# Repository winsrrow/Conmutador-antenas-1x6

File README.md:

# Conmutador antenas 1x6
Conmutador de antenas 1x6 con raspberry pi pico 2W

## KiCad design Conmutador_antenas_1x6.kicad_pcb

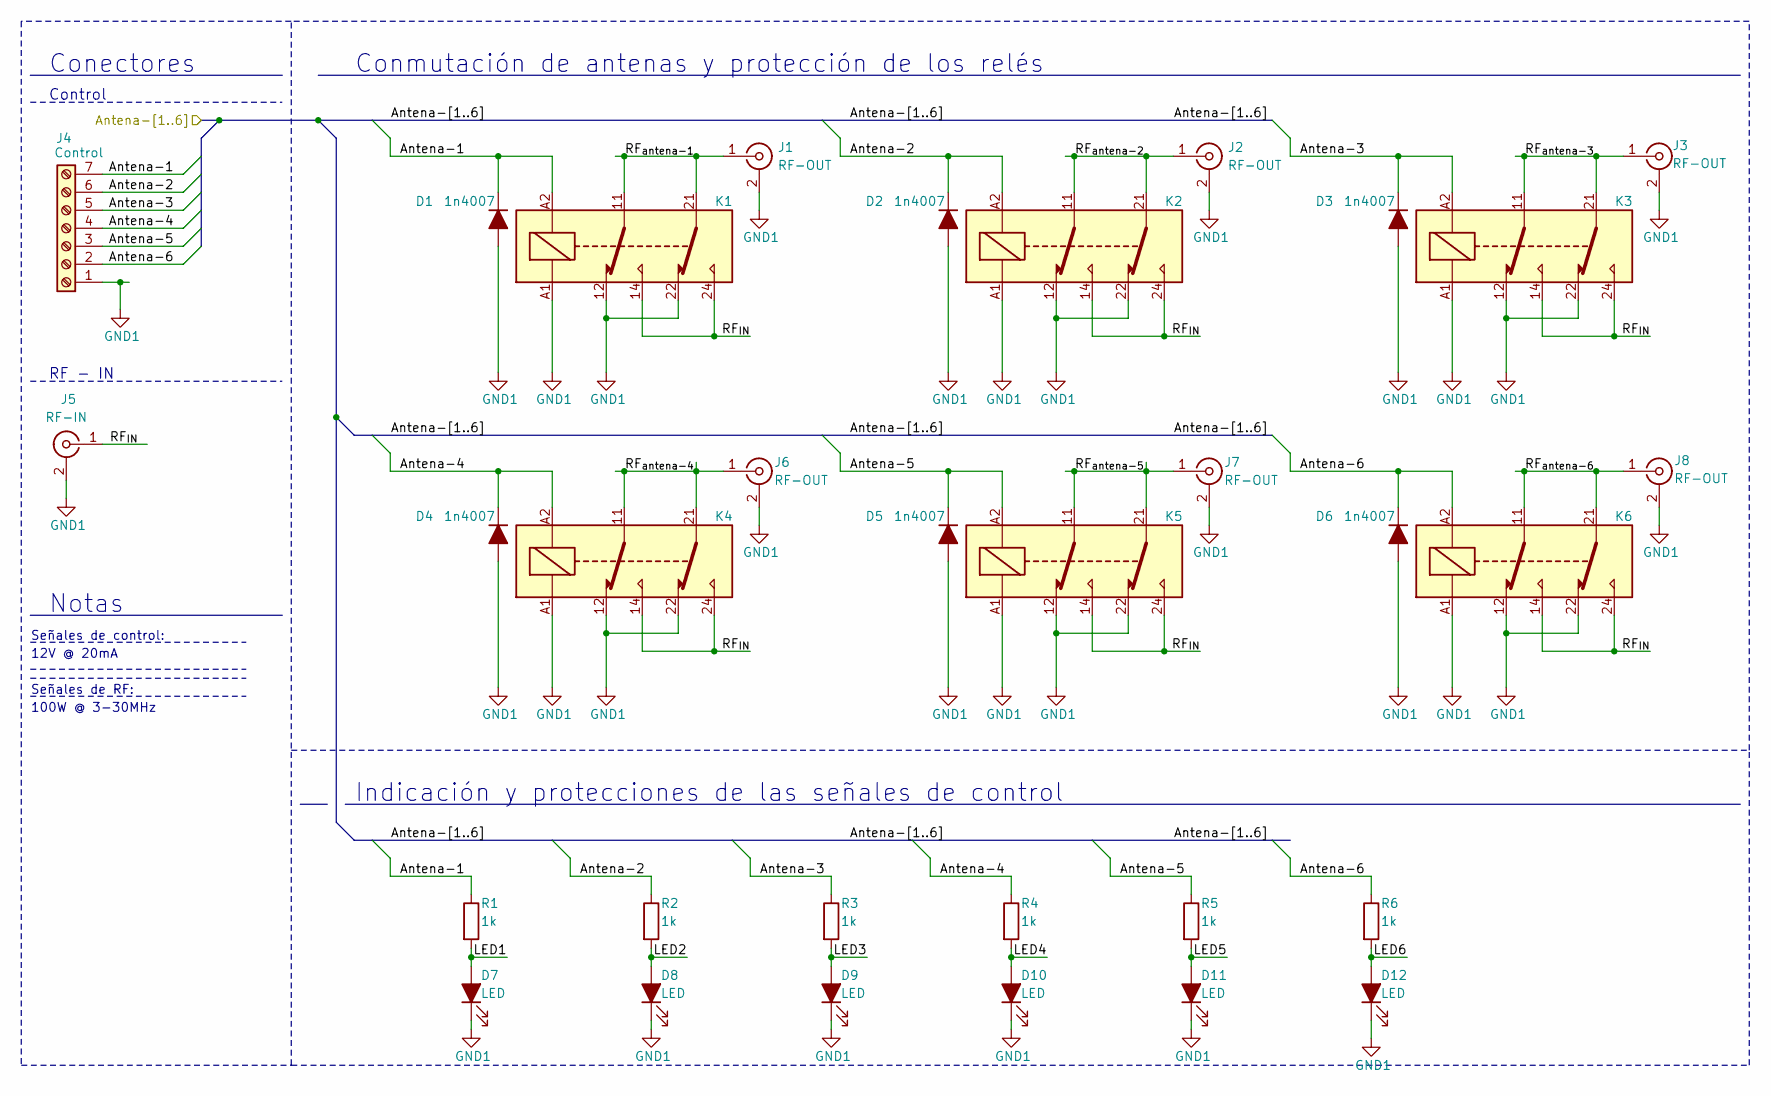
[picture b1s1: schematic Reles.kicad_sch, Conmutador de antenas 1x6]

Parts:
D1, D2, D3, D4, D5, D6: 1n4007; D_DO-41_SOD81_P7.62mm_Horizontal
D7, D8, D9, D10, D11, D12: LED; LED_D3.0mm
J1, J2, J3, J5, J6, J7, J8: Conn_Coaxial; SO-239
J4: Screw_Terminal_01x07; TerminalBlock_Phoenix_MKDS-1,5-7-5.08_1x07_P5.08mm_Horizont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
K1, K2, K3, K4, K5, K6: Relay_DPDT_Schrack-RT2-FormC_RM5mm
R1, R2, R3, R4, R5, R6: 1k; R_Axial_DIN0204_L3.6mm_D1.6mm_P5.08mm_Horizontal

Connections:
/Controlador/OUT_{1}: D1.1 (K), J4.7, K1.A2, R1.1; also elsewhere on the board
/Controlador/OUT_{2}: D2.1 (K), J4.6, K2.A2, R2.1; also elsewhere on the board
/Controlador/OUT_{3}: D3.1 (K), J4.5, K3.A2, R3.1; also elsewhere on the board
/Controlador/OUT_{4}: D4.1 (K), J4.4, K4.A2, R4.1; also elsewhere on the board
/Controlador/OUT_{5}: D5.1 (K), J4.3, K5.A2, R5.1; also elsewhere on the board
/Controlador/OUT_{6}: D6.1 (K), J4.2, K6.A2, R6.1; also elsewhere on the board
/Reles/LED1: D7.2 (A), R1.2
/Reles/LED2: D8.2 (A), R2.2
/Reles/LED3: D9.2 (A), R3.2
/Reles/LED4: D10.2 (A), R4.2
/Reles/LED5: D11.2 (A), R5.2
/Reles/LED6: D12.2 (A), R6.2
/Reles/RF_{IN}: J5.1 (In), K1.14, K1.24, K2.14, K2.24, K3.14, K3.24, K4.14, K4.24, K5.14, K5.24, K6.14, K6.24
/Reles/RF_{antena-1}: J1.1 (In), K1.11, K1.21
/Reles/RF_{antena-2}: J2.1 (In), K2.11, K2.21
/Reles/RF_{antena-3}: J3.1 (In), K3.11, K3.21
/Reles/RF_{antena-4}: J6.1 (In), K4.11, K4.21
/Reles/RF_{antena-5}: J7.1 (In), K5.11, K5.21
/Reles/RF_{antena-6}: J8.1 (In), K6.11, K6.21
GND1: D1.2 (A), D2.2 (A), D3.2 (A), D4.2 (A), D5.2 (A), D6.2 (A), D7.1 (K), D8.1 (K), D9.1 (K), D10.1 (K), D11.1 (K), D12.1 (K), J1.2 (Ext), J2.2 (Ext), J3.2 (Ext), J4.1, J5.2 (Ext), J6.2 (Ext), J7.2 (Ext), J8.2 (Ext), K1.12, K1.22, K1.A1, K2.12, K2.22, K2.A1, K3.12, K3.22, K3.A1, K4.12, K4.22, K4.A1, K5.12, K5.22, K5.A1, K6.12, K6.22, K6.A1; also elsewhere on the board

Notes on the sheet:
RF - IN
Conmutación de antenas y protección de los relés
Indicación y protecciones de las señales de control
Notas
Señales de RF:
Control
Conectores
12V @ 20mA
Señales de control:
100W @ 3-30MHz

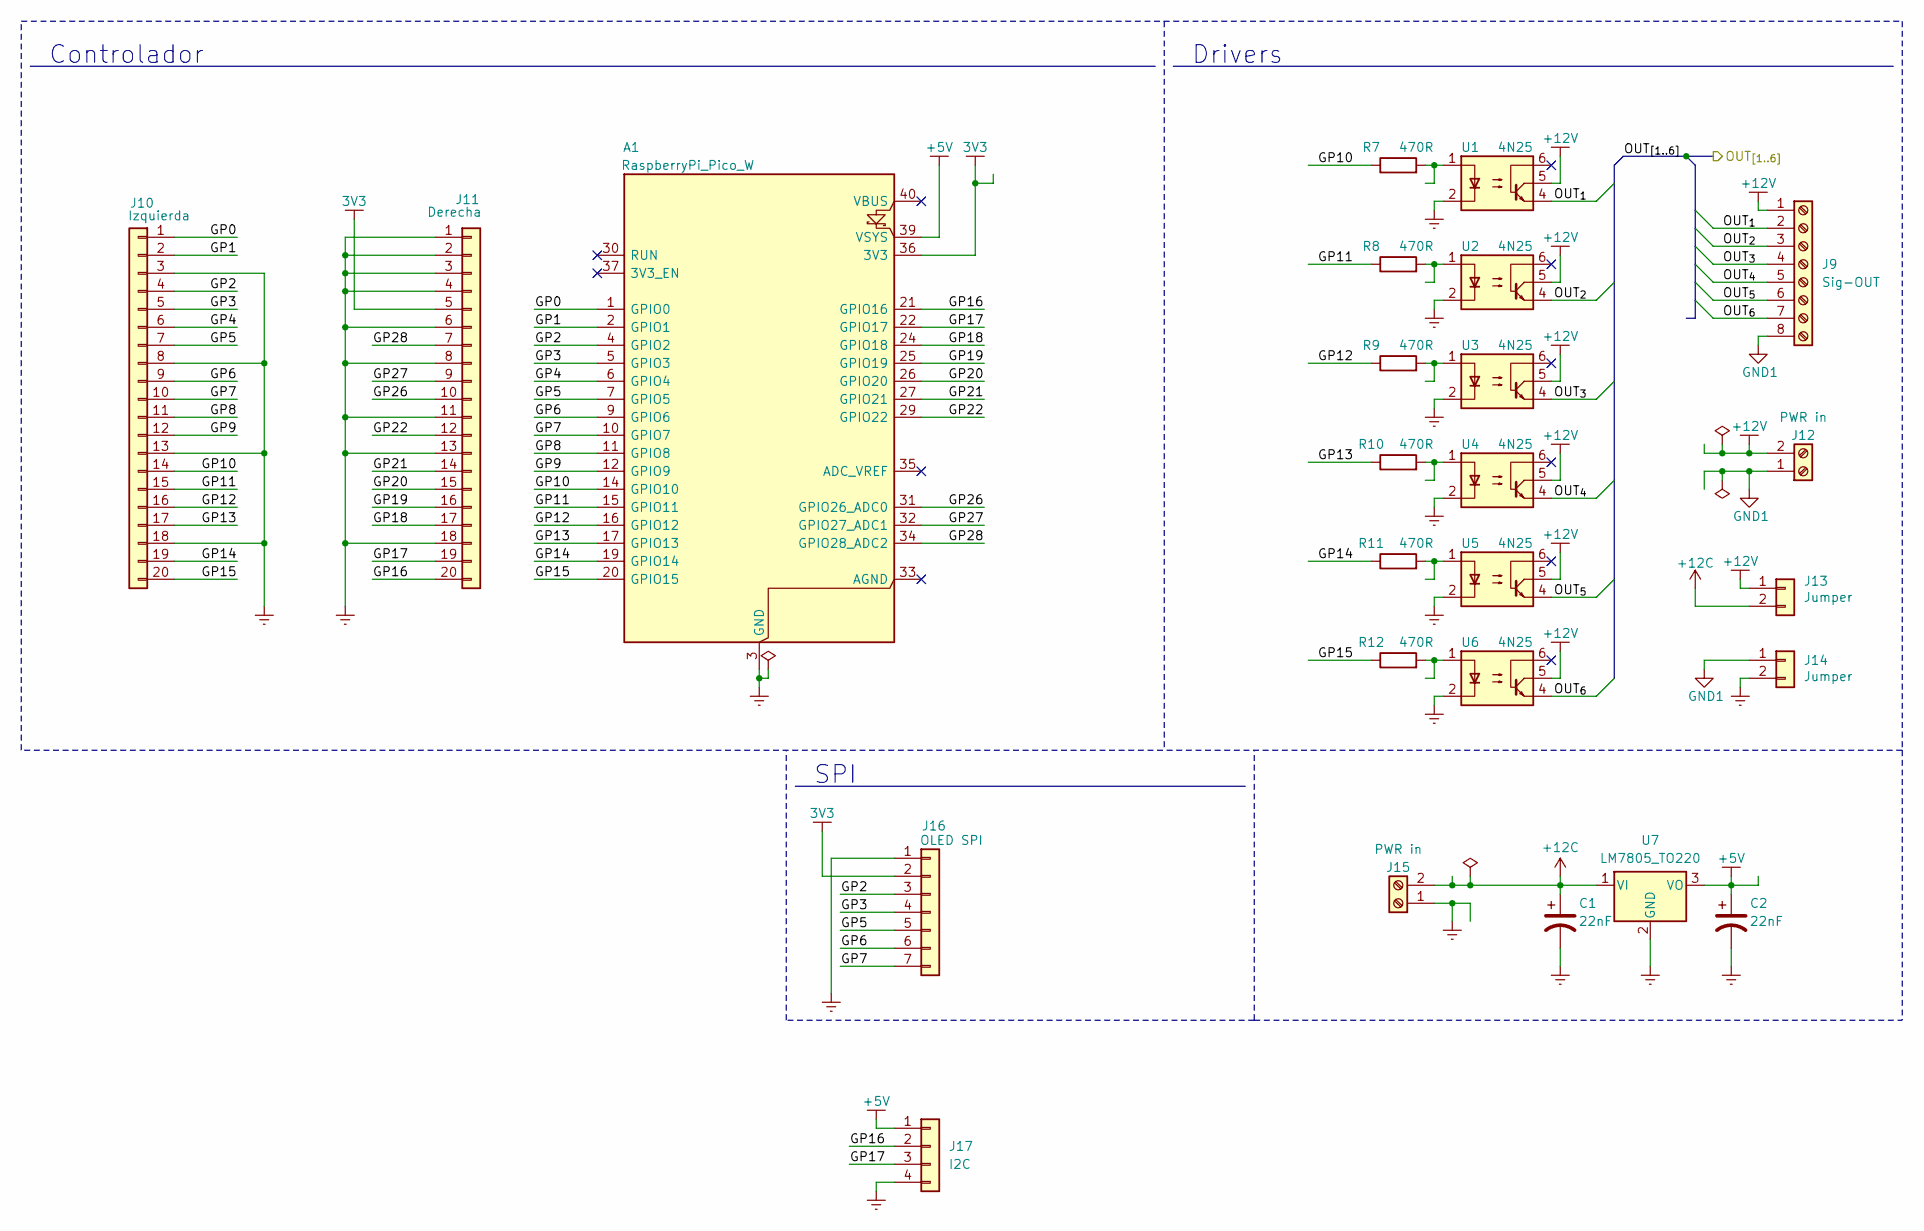
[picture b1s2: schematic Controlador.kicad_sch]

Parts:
A1: RaspberryPi_Pico_W; Pi pico 2w pin
C1, C2: 22nF; C_Disc_D5.0mm_W2.5mm_P5.00mm
J9: Screw_Terminal_01x08; TerminalBlock_Phoenix_MKDS-1,5-8-5.08_1x08_P5.08mm_Horizont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
J10, J11: Conn_01x20; PinHeader_1x20_P2.54mm_Vertical
J12, J15: Screw_Terminal_01x02; TerminalBlock_Phoenix_MKDS-1,5-2-5.08_1x02_P5.08mm_Horizont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
J13, J14: Conn_01x02; PinHeader_1x02_P2.54mm_Vertical
J16: Conn_01x07; PinHeader_1x07_P2.54mm_Vertical
J17: Conn_01x04; PinHeader_1x04_P2.54mm_Vertical
R7, R8, R9, R10, R11, R12: 470R; R_Axial_DIN0204_L3.6mm_D1.6mm_P7.62mm_Horizontal
U1, U2, U3, U4, U5, U6: 4N25; DIP-6_W7.62mm
U7: LM7805_TO220; TO-220-3_Vertical

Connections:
3V3: A1.36 (3V3), J11.5, J16.2
+5V: A1.39 (VSYS), C2.1, J17.1, U7.3 (VO)
+12C: C1.1, J13.2, J15.2, U7.1 (VI)
+12V: J9.1, J12.2, J13.1, U1.5, U2.5, U3.5, U4.5, U5.5, U6.5
/Controlador/GP0: A1.1 (GPIO0), J10.1
/Controlador/GP1: A1.2 (GPIO1), J10.2
/Controlador/GP2: A1.4 (GPIO2), J10.4, J16.3
/Controlador/GP3: A1.5 (GPIO3), J10.5, J16.4
/Controlador/GP4: A1.6 (GPIO4), J10.6
/Controlador/GP5: A1.7 (GPIO5), J10.7, J16.5
/Controlador/GP6: A1.9 (GPIO6), J10.9, J16.6
/Controlador/GP7: A1.10 (GPIO7), J10.10, J16.7
/Controlador/GP8: A1.11 (GPIO8), J10.11
/Controlador/GP9: A1.12 (GPIO9), J10.12
/Controlador/GP10: A1.14 (GPIO10), J10.14, R7.1
/Controlador/GP11: A1.15 (GPIO11), J10.15, R8.1
/Controlador/GP12: A1.16 (GPIO12), J10.16, R9.1
/Controlador/GP13: A1.17 (GPIO13), J10.17, R10.1
/Controlador/GP14: A1.19 (GPIO14), J10.19, R11.1
/Controlador/GP15: A1.20 (GPIO15), J10.20, R12.1
/Controlador/GP16: A1.21 (GPIO16), J11.20, J17.2
/Controlador/GP17: A1.22 (GPIO17), J11.19, J17.3
/Controlador/GP18: A1.24 (GPIO18), J11.17
/Controlador/GP19: A1.25 (GPIO19), J11.16
/Controlador/GP20: A1.26 (GPIO20), J11.15
/Controlador/GP21: A1.27 (GPIO21), J11.14
/Controlador/GP22: A1.29 (GPIO22), J11.12
/Controlador/GP26: A1.31 (GPIO26_ADC0), J11.10
/Controlador/GP27: A1.32 (GPIO27_ADC1), J11.9
/Controlador/GP28: A1.34 (GPIO28_ADC2), J11.7
/Controlador/OUT_{1}: J9.2, U1.4; also elsewhere on the board
/Controlador/OUT_{2}: J9.3, U2.4; also elsewhere on the board
/Controlador/OUT_{3}: J9.4, U3.4; also elsewhere on the board
/Controlador/OUT_{4}: J9.5, U4.4; also elsewhere on the board
/Controlador/OUT_{5}: J9.6, U5.4; also elsewhere on the board
/Controlador/OUT_{6}: J9.7, U6.4; also elsewhere on the board
GND: A1.3 (GND), A1.8 (GND), A1.13 (GND), A1.18 (GND), A1.23 (GND), A1.28 (GND), A1.38 (GND), C1.2, C2.2, J10.3, J10.8, J10.13, J10.18, J11.1, J11.2, J11.3, J11.4, J11.6, J11.8, J11.11, J11.13, J11.18, J14.2, J15.1, J16.1, J17.4, U1.2, U2.2, U3.2, U4.2, U5.2, U6.2, U7.2 (GND)
GND1: J9.8, J12.1, J14.1; also elsewhere on the board
unnamed: R7.2, U1.1
unnamed: R8.2, U2.1
unnamed: R9.2, U3.1
unnamed: R10.2, U4.1
unnamed: R11.2, U5.1
unnamed: R12.2, U6.1

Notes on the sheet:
Controlador
SPI
Drivers

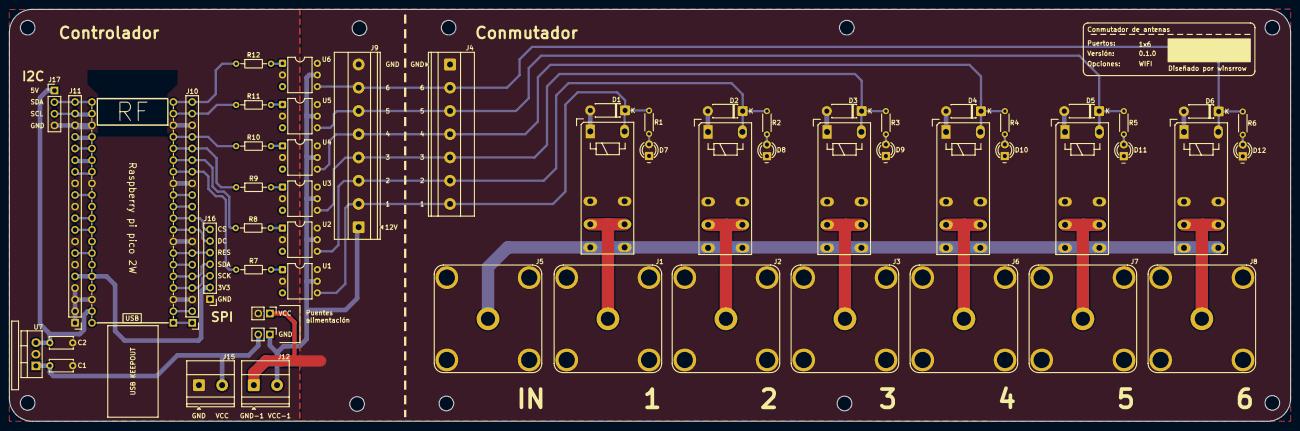
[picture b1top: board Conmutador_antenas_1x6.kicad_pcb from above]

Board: 2 copper layers, 280.0 x 90.0 mm, 57 parts (0 on the bottom side), 57 nets.

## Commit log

2025-07-27 kicad crash
2025-08-08 Finished board layout
    0.1.0
